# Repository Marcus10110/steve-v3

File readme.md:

# Steve the Bartending Robot

PCB Revision 3

Steve the bartending robot is a robotic drink maker, capable of dispensing 24 different liquids for mixing cocktails.

## Hardware Guide

### Electronics
The Steve V3 PCB design files can be found in the BarBot3 directory.

The schematics and layout were created with [KiCad](https://www.kicad.org/)

The board can also be ordered directly from [OSHPARK](https://oshpark.com/) [here](https://oshpark.com/shared_projects/AuEMTmuf).

The bill of materials for the PCB, pumps, and wire harness for the pumps is available on [octopart](https://octopart.com/) [here](https://octopart.com/bom-tool/abOfMIaY).

The design also requires a 12V, 4A+ power supply with a 5.5x2.1mm barrel jack, and a USB-C cable, for USB 2.0 data.

The power supply current rating is the limiting factor for the number of pumps which can be turned on simultaneously.

The parts list include includes wire, connectors, and crimps for assembling the pump motor wire harnesses.

Additionally, a crimp tool is needed to crimp the connectors into the wire. **TODO: find PN and place here.**

We assembled the pumps all with the same wire length, long enough to reach from the PCB to the furthest pump with some spare distance.

The connector pin 1 should be connected to the positive side of the pump, and pin 2 should be connected to the negative side.

**TODO: add wire assembly detail here**

### Mechanical

To hold all the pumps and the PCB together. This was laser cut from acrylic. The CAD design can be found on [onshape](https://www.onshape.com/en/) [here](https://cad.onshape.com/documents/0a76c84c79ce9e6492f21b7e/w/e3ece1aa1a5ce6af157ea8d7/e/032fdd28f397ef2ffe8feb1f?renderMode=0&uiState=61be55ddfef761767acffcc4).

In addition to the laser cut mount, the following parts are needed:
- [Wood Furniture Legs](https://www.amazon.com/gp/product/B07DF68BN7/ref=ppx_yo_dt_b_search_asin_image?ie=UTF8&psc=1)
- M2.5 thermal threaded inserts x48
- M3 thermal threaded inserts x3
- 3/4 inch wood screws #8 x4
- M2.5 screws x48
- M3 standoffs x3
- M3 screws x3

**TODO: add McMaster links**

### Firmware

The firmware is developed using the Arduino software, and can be found in the BarBot3Firmware folder.

The hardware implementation was based off of Sparkfun's [SparkFun Qwiic Pro Micro](https://www.sparkfun.com/products/15795), which is essentially a Sparkfun Pro Micro but with a USB-C connector.

In the arduino software, you will want to install the Sparkfun board library, and select the Sparkfun Pro Micro 3.3V / 8 MHz board. Install instructions can be found [here](https://github.com/sparkfun/Arduino_Boards#installation-instructions).

Also, install the "Adafruit MCP23008 Library" from the library manager.

It's important to mention that the microcontroller does not support USB bus power, so the 12V power supply must be connected in order for the microcontroller to run.

Before the firmware can be loaded onto the microcontroller, the Arduino bootloader needs to be loaded onto the ATMEGA32U4. This can be done in a number of ways, however the simplest is to use the AVR-ISP MK2.

**TODO: link to an actually good FW flashing article**

Once the Arduino bootloader has been flashed, the device should enumerate as a serial port over USB.

The BarBot3Firmware project should compile successfully once the required library is installed. Be sure the board mentioned above is selected. Then download the firmware.

To verify the design is working, open the serial monitor in the Arduino software, and type and send "DEBUG". This will print out a list of 24 zeros, indicating that all pumps are off. This command is for debugging only, and prints out the number of milliseconds each pump will remain on. Once a pump reaches zero, the pump will turn off.

Refer to the comments at the top of BarBat3Firmware.ino for documentation on the supported commands

**TODO: move firmware command documentation here**

### Software

**TODO: Link to SW repository here.**

## Operating Guide

**TODO: write operating guide here**

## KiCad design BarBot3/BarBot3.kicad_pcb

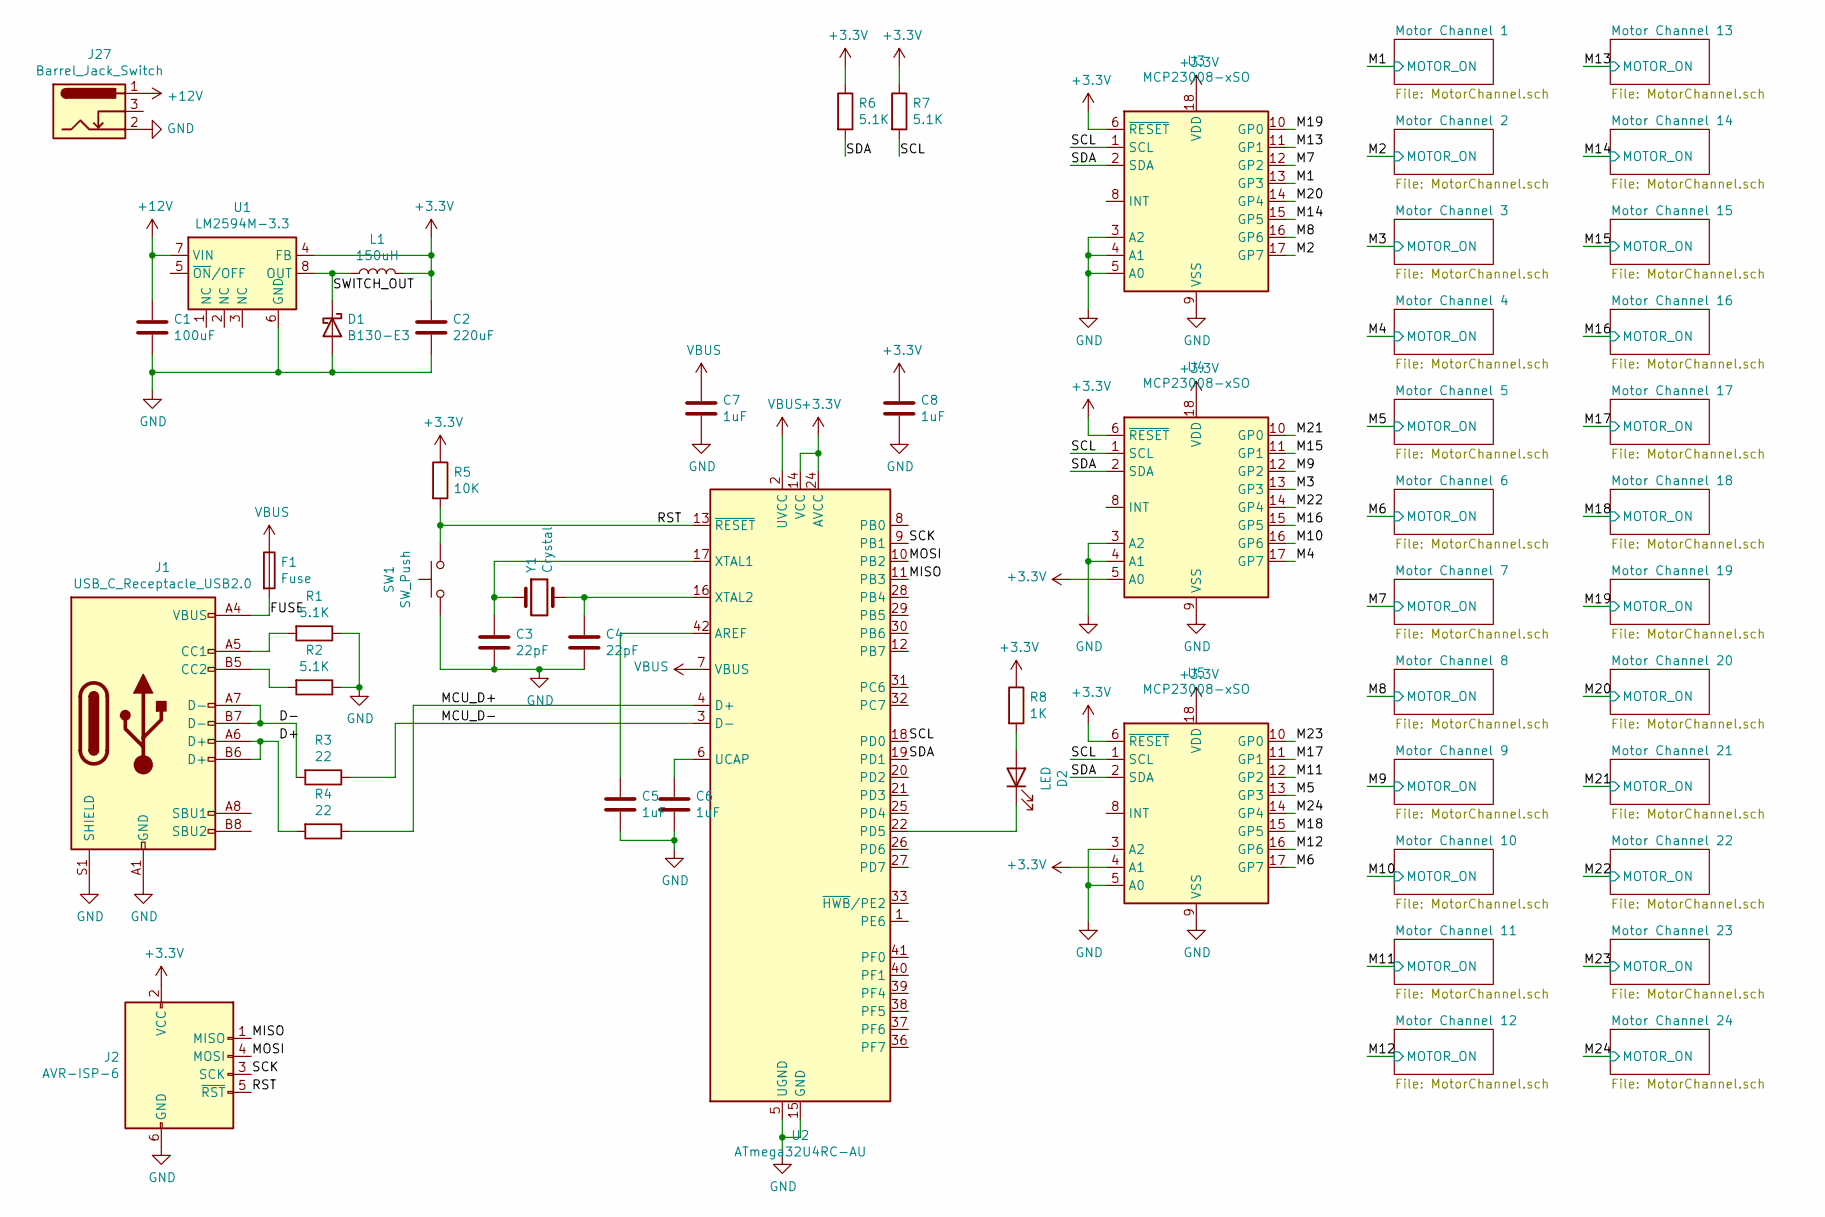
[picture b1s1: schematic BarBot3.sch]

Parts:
C1: 100uF; C_Elec_8x10.2
C2: 220uF; CP_Elec_10x10
C3, C4: 22pF; C_0805_2012Metric_Pad1.18x1.45mm_HandSolder
C5, C6, C7, C8: 1uF; C_0805_2012Metric_Pad1.18x1.45mm_HandSolder
D1: B130-E3; D_SOD-123
D2: LED; LED_PLCC-2
F1: Fuse; Fuse_1206_3216Metric_Pad1.42x1.75mm_HandSolder
J1: USB_C_Receptacle_USB2.0; USB_C_Receptacle_GCT_USB4085
J2: AVR-ISP-6; PinHeader_2x03_P2.54mm_Vertical
J27: Barrel_Jack_Switch; BarrelJack_CUI_PJ-102AH_Horizontal
L1: 150uH; L_Bourns_SRR1210A
R1, R2, R6, R7: 5.1K; R_0805_2012Metric_Pad1.20x1.40mm_HandSolder
R3, R4: 22; R_0805_2012Metric_Pad1.20x1.40mm_HandSolder
R5: 10K; R_0805_2012Metric_Pad1.20x1.40mm_HandSolder
R8: 1K; R_0805_2012Metric_Pad1.20x1.40mm_HandSolder
SW1: SW_Push; SW_Push_1P1T_NO_6x6mm_H9.5mm
U1: LM2594M-3.3; SOIC-8_3.9x4.9mm_P1.27mm
U2: ATmega32U4RC-AU; TQFP-44_10x10mm_P0.8mm
U3, U4, U5: MCP23008-xSO; SOIC-18W_7.5x11.6mm_P1.27mm
Y1: Crystal; Crystal_SMD_HC49-SD_HandSoldering

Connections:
+3V3: C2.1, C8.1, J2.2 (VCC), L1.2, R5.1, R6.1, R7.1, R8.1, U1.4 (FB), U2.14 (VCC), U2.24 (AVCC), U2.34 (VCC), U2.44 (AVCC), U3.6 (~RESET), U3.18 (VDD), U4.5 (A0), U4.6 (~RESET), U4.18 (VDD), U5.4 (A1), U5.6 (~RESET), U5.18 (VDD)
+12V: C1.1, J27.1, U1.7 (VIN); also elsewhere on the board
/D+: J1.A6 (D+), J1.B6 (D+), R4.2
/D-: J1.A7 (D-), J1.B7 (D-), R3.2
/FUSE: F1.2, J1.A4 (VBUS), J1.A9 (VBUS), J1.B4 (VBUS), J1.B9 (VBUS)
/M1: U3.13 (GP3); also elsewhere on the board
/M2: U3.17 (GP7); also elsewhere on the board
/M3: U4.13 (GP3); also elsewhere on the board
/M4: U4.17 (GP7); also elsewhere on the board
/M5: U5.13 (GP3); also elsewhere on the board
/M6: U5.17 (GP7); also elsewhere on the board
/M7: U3.12 (GP2); also elsewhere on the board
/M8: U3.16 (GP6); also elsewhere on the board
/M9: U4.12 (GP2); also elsewhere on the board
/M10: U4.16 (GP6); also elsewhere on the board
/M11: U5.12 (GP2); also elsewhere on the board
/M12: U5.16 (GP6); also elsewhere on the board
/M13: U3.11 (GP1); also elsewhere on the board
/M14: U3.15 (GP5); also elsewhere on the board
/M15: U4.11 (GP1); also elsewhere on the board
/M16: U4.15 (GP5); also elsewhere on the board
/M17: U5.11 (GP1); also elsewhere on the board
/M18: U5.15 (GP5); also elsewhere on the board
/M19: U3.10 (GP0); also elsewhere on the board
/M20: U3.14 (GP4); also elsewhere on the board
/M21: U4.10 (GP0); also elsewhere on the board
/M22: U4.14 (GP4); also elsewhere on the board
/M23: U5.10 (GP0); also elsewhere on the board
/M24: U5.14 (GP4); also elsewhere on the board
/MCU_D+: R4.1, U2.4 (D+)
/MCU_D-: R3.1, U2.3 (D-)
/MISO: J2.1 (MISO), U2.11 (PB3)
/MOSI: J2.4 (MOSI), U2.10 (PB2)
/RST: J2.5 (~RST), R5.2, SW1.2, U2.13 (~RESET)
/SCK: J2.3 (SCK), U2.9 (PB1)
/SCL: R7.2, U2.18 (PD0), U3.1 (SCL), U4.1 (SCL), U5.1 (SCL)
/SDA: R6.2, U2.19 (PD1), U3.2 (SDA), U4.2 (SDA), U5.2 (SDA)
/SWITCH_OUT: D1.1 (K), L1.1, U1.8 (OUT)
GND: C1.2, C2.2, C3.2, C4.2, C5.2, C6.2, C7.2, C8.2, D1.2 (A), J1.A1 (GND), J1.A12 (GND), J1.B1 (GND), J1.B12 (GND), J1.S1 (SHIELD), J2.6 (GND), J27.2, R1.1, R2.1, SW1.1, U1.6 (GND), U2.5 (UGND), U2.15 (GND), U2.23 (GND), U2.35 (GND), U2.43 (GND), U3.3 (A2), U3.4 (A1), U3.5 (A0), U3.9 (VSS), U4.3 (A2), U4.4 (A1), U4.9 (VSS), U5.3 (A2), U5.5 (A0), U5.9 (VSS); also elsewhere on the board
unnamed: C3.1, U2.17 (XTAL1), Y1.1
unnamed: C4.1, U2.16 (XTAL2), Y1.2
unnamed: C5.1, U2.42 (AREF)
unnamed: C6.1, U2.6 (UCAP)
unnamed: D2.1 (K), U2.22 (PD5)
unnamed: D2.2 (A), R8.2
unnamed: J1.A5 (CC1), R1.2
unnamed: J1.B5 (CC2), R2.2
VBUS: C7.1, F1.1, U2.2 (UVCC), U2.7 (VBUS)

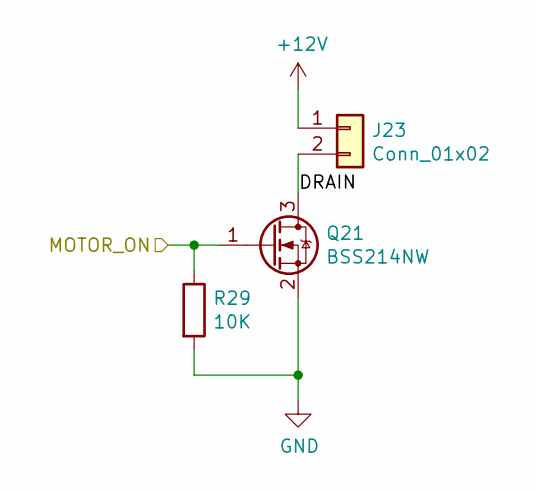
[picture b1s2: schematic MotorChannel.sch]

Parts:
J3: Conn_01x02; Hirose_DF3EA-02P-2V_1x02-1MP_P2.00mm_Vertical
Q1: BSS214NW; SOT-323_SC-70
R9: 10K; R_0805_2012Metric_Pad1.20x1.40mm_HandSolder

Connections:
+12V: J3.1; also elsewhere on the board
/M1: Q1.1 (G), R9.1; also elsewhere on the board
/Motor Channel 1/DRAIN: J3.2, Q1.3 (D)
GND: Q1.2 (S), R9.2; also elsewhere on the board

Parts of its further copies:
J4, J5, J6, J7, J8, J9, J10, J11, J12, J13, J14, J15, J16, J17, J18, J19, J20, J21, J22, J23, J24, J25, J26: Conn_01x02; Hirose_DF3EA-02P-2V_1x02-1MP_P2.00mm_Vertical
Q2, Q3, Q4, Q5, Q6, Q7, Q8, Q9, Q10, Q11, Q12, Q13, Q14, Q15, Q16, Q17, Q18, Q19, Q20, Q21, Q22, Q23, Q24: BSS214NW; SOT-323_SC-70
R10, R11, R12, R13, R14, R15, R16, R17, R18, R19, R20, R21, R22, R23, R24, R25, R26, R27, R28, R29, R30, R31, R32: 10K; R_0805_2012Metric_Pad1.20x1.40mm_HandSolder

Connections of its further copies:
+12V: J4.1, J5.1, J6.1, J7.1, J8.1, J9.1, J10.1, J11.1, J12.1, J13.1, J14.1, J15.1, J16.1, J17.1, J18.1, J19.1, J20.1, J21.1, J22.1, J23.1, J24.1, J25.1, J26.1; also elsewhere on the board
/M2: Q2.1 (G), R10.1; also elsewhere on the board
/M3: Q3.1 (G), R11.1; also elsewhere on the board
/M4: Q4.1 (G), R12.1; also elsewhere on the board
/M5: Q5.1 (G), R13.1; also elsewhere on the board
/M6: Q6.1 (G), R14.1; also elsewhere on the board
/M7: Q7.1 (G), R15.1; also elsewhere on the board
/M8: Q8.1 (G), R16.1; also elsewhere on the board
/M9: Q9.1 (G), R17.1; also elsewhere on the board
/M10: Q10.1 (G), R18.1; also elsewhere on the board
/M11: Q11.1 (G), R19.1; also elsewhere on the board
/M12: Q12.1 (G), R20.1; also elsewhere on the board
/M13: Q13.1 (G), R21.1; also elsewhere on the board
/M14: Q14.1 (G), R22.1; also elsewhere on the board
/M15: Q15.1 (G), R23.1; also elsewhere on the board
/M16: Q16.1 (G), R24.1; also elsewhere on the board
/M17: Q17.1 (G), R25.1; also elsewhere on the board
/M18: Q18.1 (G), R26.1; also elsewhere on the board
/M19: Q19.1 (G), R27.1; also elsewhere on the board
/M20: Q20.1 (G), R28.1; also elsewhere on the board
/M21: Q21.1 (G), R29.1; also elsewhere on the board
/M22: Q22.1 (G), R30.1; also elsewhere on the board
/M23: Q23.1 (G), R31.1; also elsewhere on the board
/M24: Q24.1 (G), R32.1; also elsewhere on the board
/Motor Channel 2/DRAIN: J4.2, Q2.3 (D)
/Motor Channel 3/DRAIN: J5.2, Q3.3 (D)
/Motor Channel 4/DRAIN: J6.2, Q4.3 (D)
/Motor Channel 5/DRAIN: J7.2, Q5.3 (D)
/Motor Channel 6/DRAIN: J8.2, Q6.3 (D)
/Motor Channel 7/DRAIN: J9.2, Q7.3 (D)
/Motor Channel 8/DRAIN: J10.2, Q8.3 (D)
/Motor Channel 9/DRAIN: J11.2, Q9.3 (D)
/Motor Channel 10/DRAIN: J12.2, Q10.3 (D)
/Motor Channel 11/DRAIN: J13.2, Q11.3 (D)
/Motor Channel 12/DRAIN: J14.2, Q12.3 (D)
/Motor Channel 13/DRAIN: J15.2, Q13.3 (D)
/Motor Channel 14/DRAIN: J16.2, Q14.3 (D)
/Motor Channel 15/DRAIN: J17.2, Q15.3 (D)
/Motor Channel 16/DRAIN: J18.2, Q16.3 (D)
/Motor Channel 17/DRAIN: J19.2, Q17.3 (D)
/Motor Channel 18/DRAIN: J20.2, Q18.3 (D)
/Motor Channel 19/DRAIN: J21.2, Q19.3 (D)
/Motor Channel 20/DRAIN: J22.2, Q20.3 (D)
/Motor Channel 21/DRAIN: J23.2, Q21.3 (D)
/Motor Channel 22/DRAIN: J24.2, Q22.3 (D)
/Motor Channel 23/DRAIN: J25.2, Q23.3 (D)
/Motor Channel 24/DRAIN: J26.2, Q24.3 (D)
GND: Q2.2 (S), Q3.2 (S), Q4.2 (S), Q5.2 (S), Q6.2 (S), Q7.2 (S), Q8.2 (S), Q9.2 (S), Q10.2 (S), Q11.2 (S), Q12.2 (S), Q13.2 (S), Q14.2 (S), Q15.2 (S), Q16.2 (S), Q17.2 (S), Q18.2 (S), Q19.2 (S), Q20.2 (S), Q21.2 (S), Q22.2 (S), Q23.2 (S), Q24.2 (S), R10.2, R11.2, R12.2, R13.2, R14.2, R15.2, R16.2, R17.2, R18.2, R19.2, R20.2, R21.2, R22.2, R23.2, R24.2, R25.2, R26.2, R27.2, R28.2, R29.2, R30.2, R31.2, R32.2; also elsewhere on the board

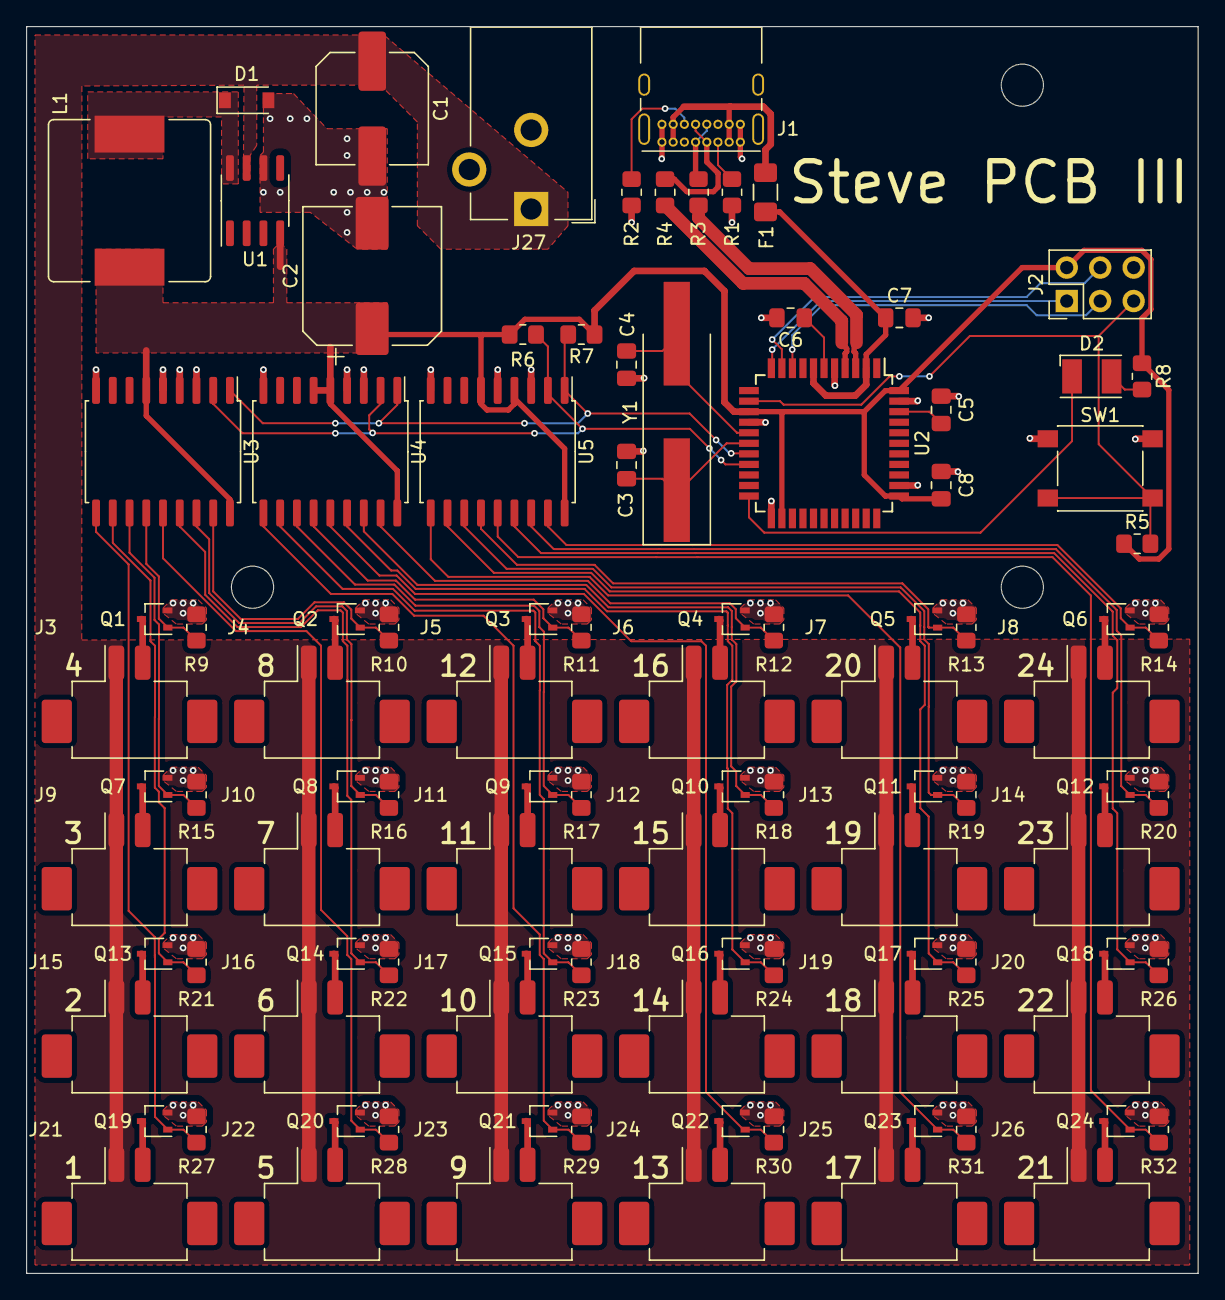
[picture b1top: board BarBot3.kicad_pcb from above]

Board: 2 copper layers, 88.9 x 94.6 mm, 102 parts (0 on the bottom side), 72 nets.

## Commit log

2021-11-14 First commit. This version was submitted for fabrication
2021-11-30 added arduino firmware
2021-12-05 added firmware usage documentation.
2021-12-18 updated the readme. Still a lot of missing content.
